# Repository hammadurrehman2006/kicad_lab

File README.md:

# kicad_lab
A collection of KiCad PCB designs developed during my Electronic Engineering degree (2024-28). Includes university projects, personal experiments, and custom components—featuring schematics, layouts, Gerber files, and documentation. Open-source hardware for education, collaboration, and real-world manufacturing.

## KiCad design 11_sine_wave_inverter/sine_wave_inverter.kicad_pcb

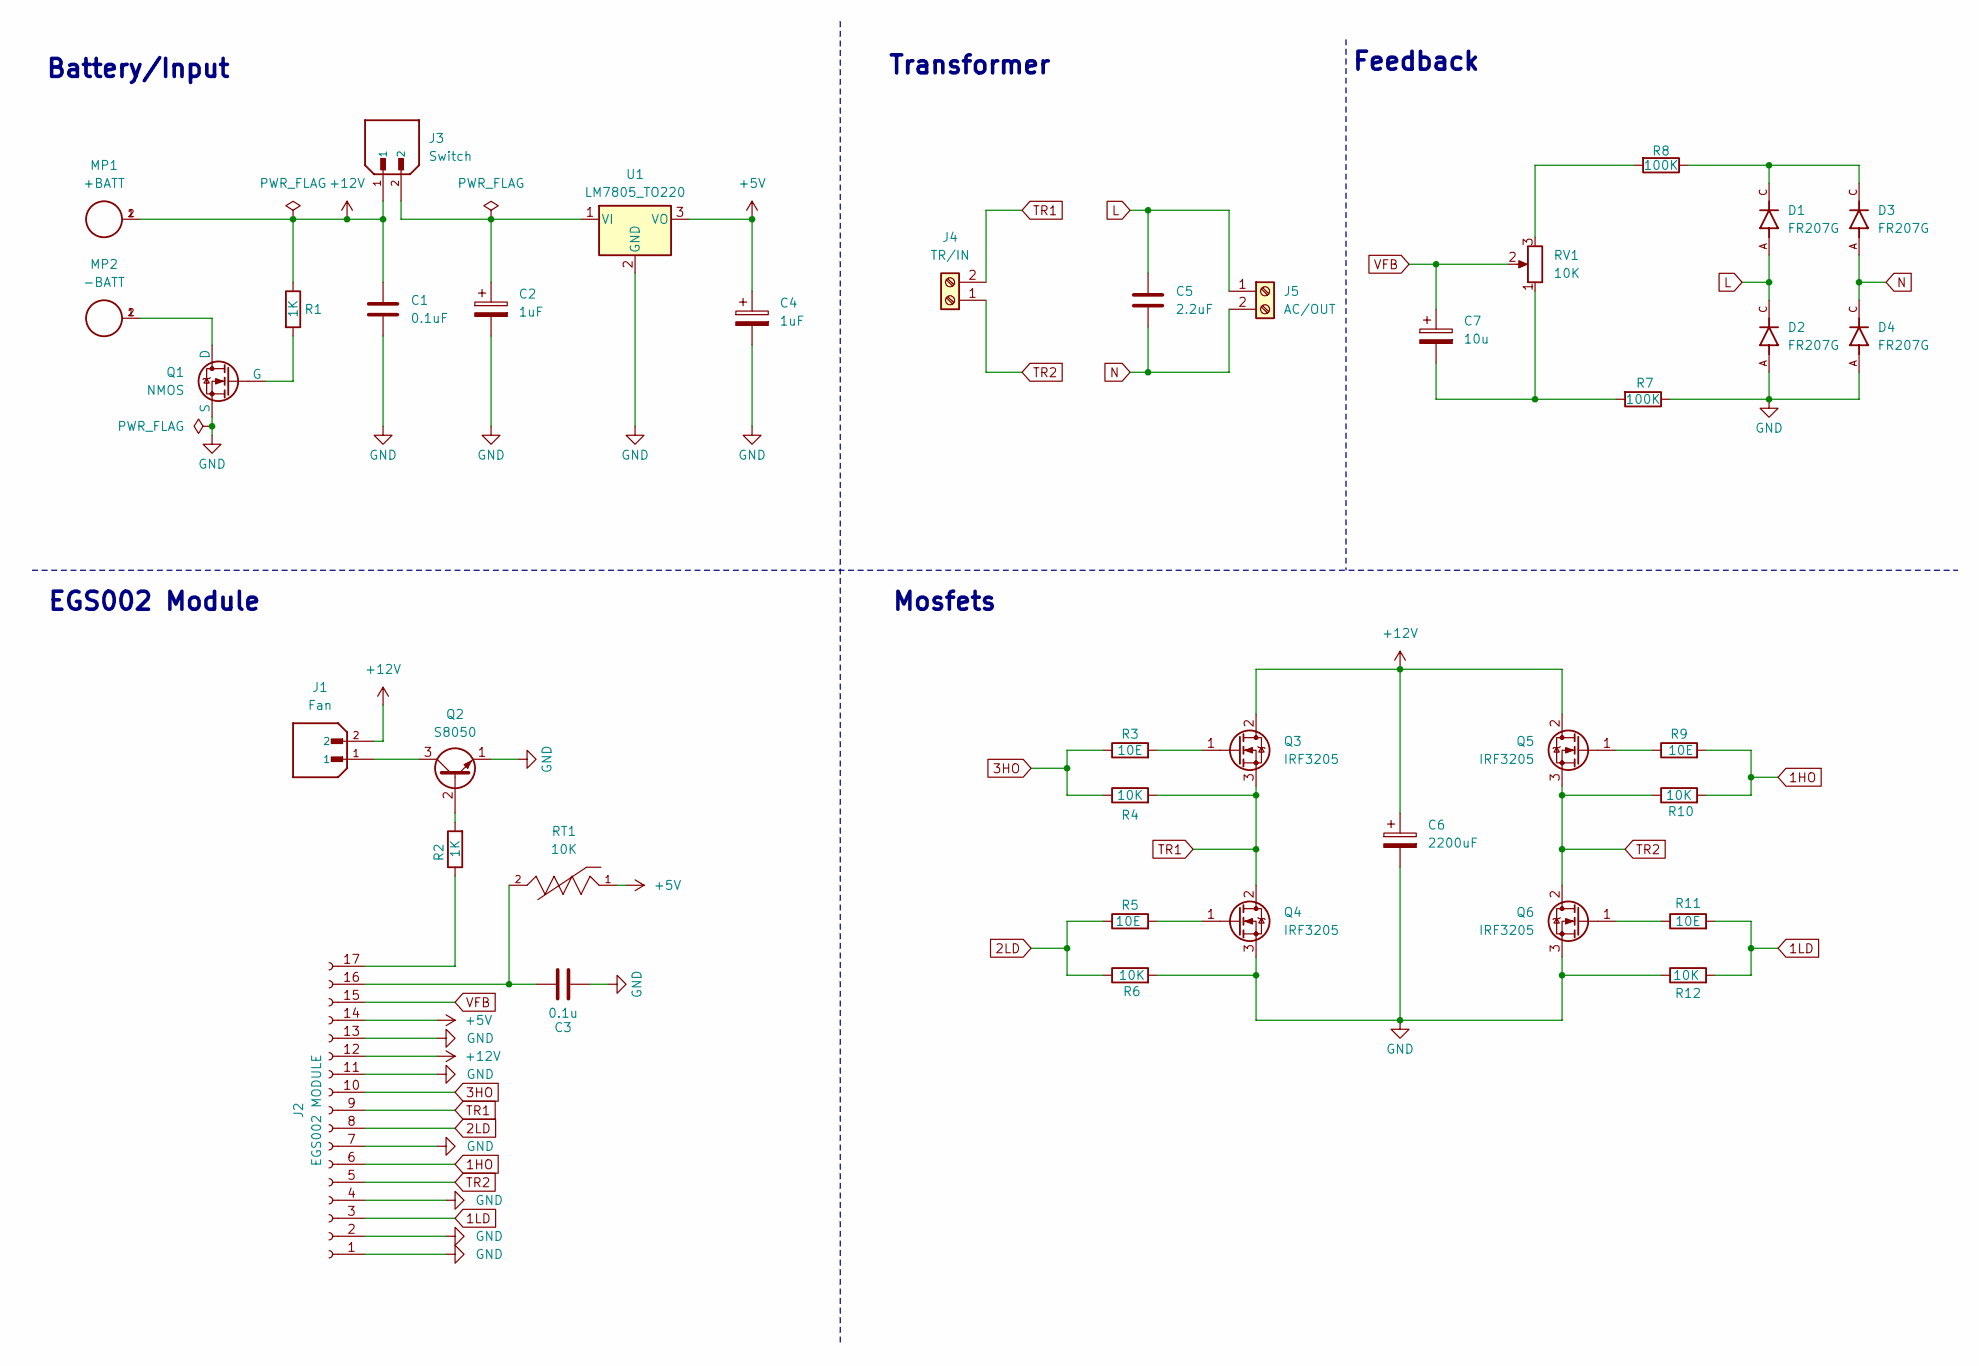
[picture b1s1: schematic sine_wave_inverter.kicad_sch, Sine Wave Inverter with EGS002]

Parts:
C1: 0.1uF; C_Disc_D4.3mm_W1.9mm_P5.00mm
C2, C4: 1uF; CP_Radial_D5.0mm_P2.50mm
C3: 0.1u; C_Disc_D4.3mm_W1.9mm_P5.00mm
C5: 2.2uF; C_Rect_L16.5mm_W6.0mm_P15.00mm_MKT
C6: 2200uF; CP_Radial_D12.5mm_P5.00mm
C7: 10u; CP_Radial_D5.0mm_P2.50mm
D1, D2, D3, D4: FR207G; DIOAD1300W80L670D310; PARTREV F2105
J1: Fan; JST_B2B-XH-A__LF__SN_; PARTREV N/A
J2: EGS002 MODULE; PinSocket_1x17_P2.54mm_Vertical
J3: Switch; JST_B2B-XH-A__LF__SN_; PARTREV N/A
J4: TR/IN; TerminalBlock_bornier-2_P5.08mm
J5: AC/OUT; TerminalBlock_bornier-2_P5.08mm
MP1: +BATT; WA-MTAB_7471287; PART-NUMBER 7471287
MP2: -BATT; WA-MTAB_7471287; PART-NUMBER 7471287
Q1: NMOS; TO-252-2
Q2: S8050; TO-92_Inline
Q3, Q4, Q5, Q6: IRF3205; TO-220-3_Vertical
R1, R2: 1K; R_Axial_DIN0207_L6.3mm_D2.5mm_P7.62mm_Horizontal
R3, R5, R9, R11: 10E; R_Axial_DIN0207_L6.3mm_D2.5mm_P7.62mm_Horizontal
R4, R6, R10, R12: 10K; R_Axial_DIN0207_L6.3mm_D2.5mm_P7.62mm_Horizontal
R7, R8: 100K; R_Axial_DIN0207_L6.3mm_D2.5mm_P7.62mm_Horizontal
RT1: 10K; THERM_NXRT15WB333JA3A016; PARTREV N/A
RV1: 10K; Potentiometer_Bourns_3296W_Vertical
U1: LM7805_TO220; TO-220-3_Vertical

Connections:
1HO: J2.6, R9.2, R10.2
1LD: J2.3, R11.2, R12.2
2LD: J2.8, R5.1, R6.1
3HO: J2.10, R3.1, R4.1
+5V: C4.1, J2.14, RT1.1, U1.3 (VO)
+12V: C1.1, C6.1, J1.2, J2.12, J3.1, MP1.1, MP1.2, Q3.2 (D), Q5.2 (D), R1.1
GND: C1.2, C2.2, C3.2, C4.2, C6.2, D2.A, D4.A, J2.1, J2.2, J2.4, J2.7, J2.11, J2.13, Q1.3 (S), Q2.1 (E), Q4.3 (S), Q6.3 (S), R6.2, R7.1, R12.1, U1.2 (GND)
L: C5.1, D1.A, D2.C, J5.1
N: C5.2, D3.A, D4.C, J5.2
unnamed: C7.2, R7.2, RV1.1
unnamed: D1.C, D3.C, R8.1
unnamed: C3.1, J2.16, RT1.2
unnamed: J2.17, R2.1
unnamed: MP2.1, MP2.2, Q1.1 (D)
unnamed: Q1.2 (G), R1.2
unnamed: Q2.2 (B), R2.2
unnamed: J1.1, Q2.3 (C)
unnamed: Q3.1 (G), R3.2
unnamed: Q4.1 (G), R5.2
unnamed: Q5.1 (G), R9.1
unnamed: Q6.1 (G), R11.1
unnamed: R8.2, RV1.3
unnamed: C2.1, J3.2, U1.1 (VI)
TR1: J2.9, J4.2, Q3.3 (S), Q4.2 (D), R4.2
TR2: J2.5, J4.1, Q5.3 (S), Q6.2 (D), R10.1
VFB: C7.1, J2.15, RV1.2

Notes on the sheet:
Battery/Input
EGS002 Module
Transformer
Feedback
Mosfets

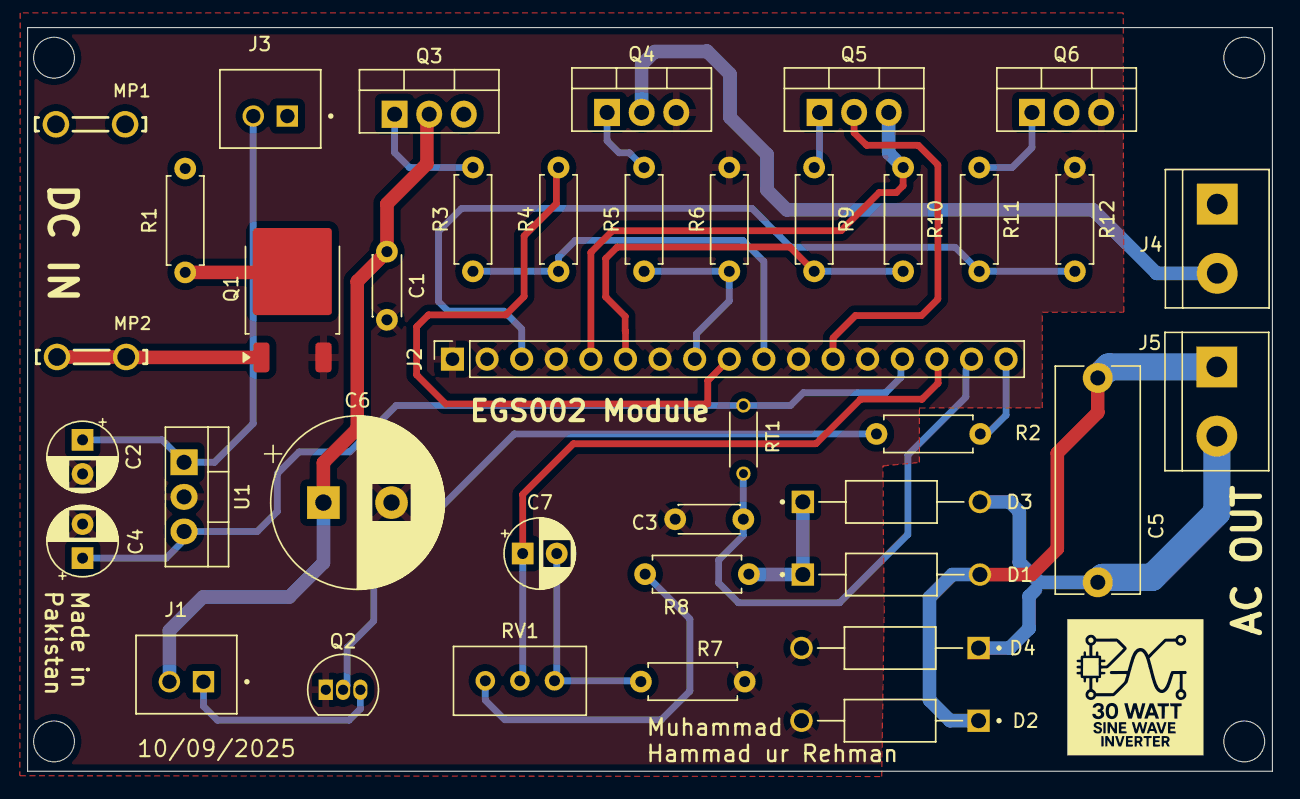
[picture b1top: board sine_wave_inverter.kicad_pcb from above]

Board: 2 copper layers, 91.4 x 54.6 mm, 39 parts (0 on the bottom side), 26 nets.

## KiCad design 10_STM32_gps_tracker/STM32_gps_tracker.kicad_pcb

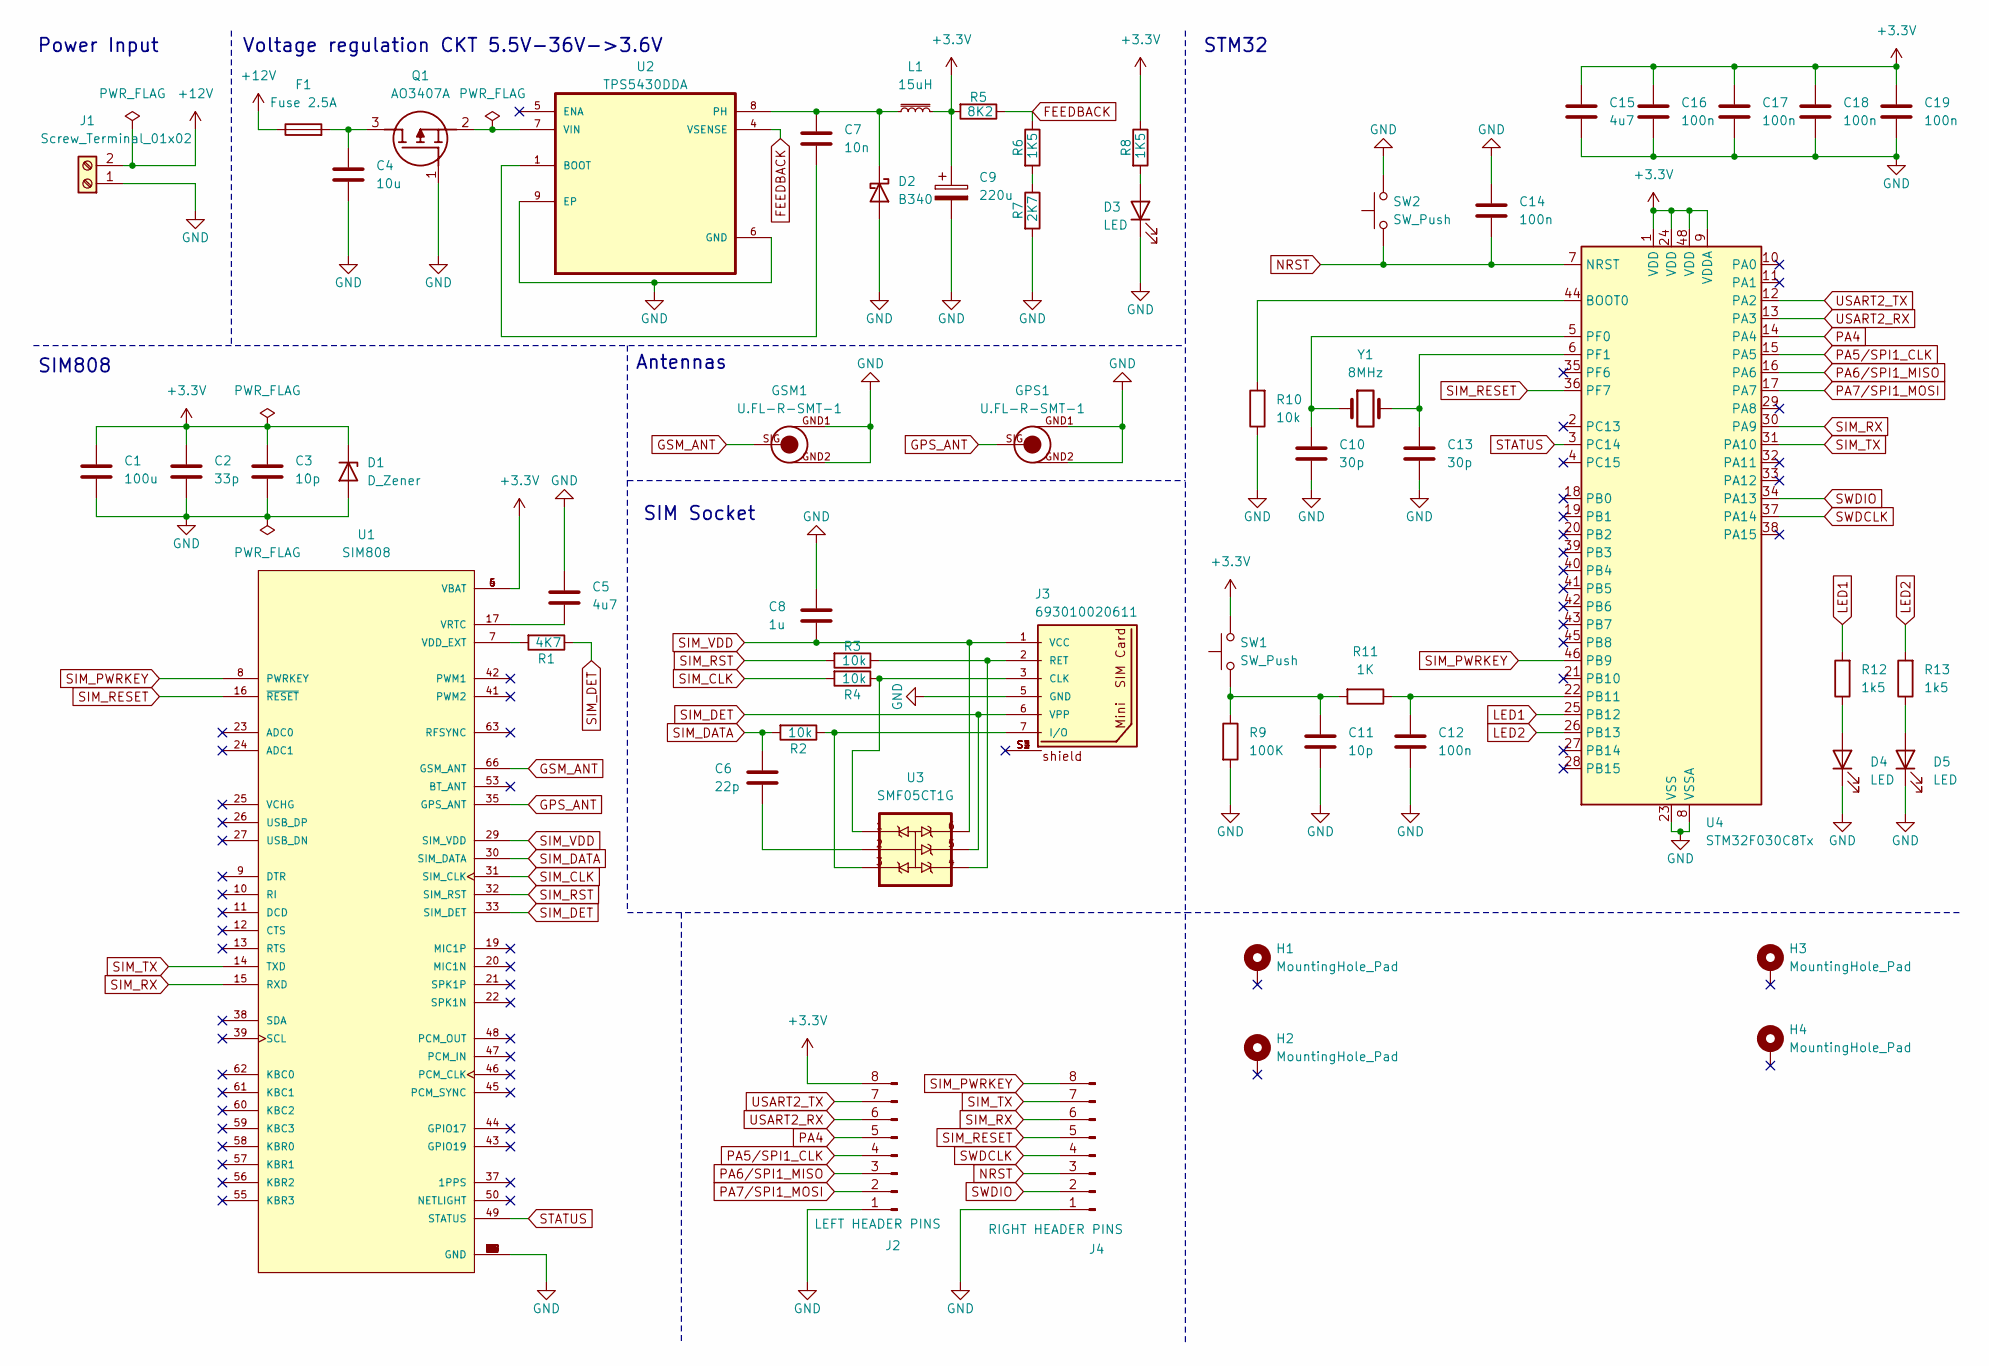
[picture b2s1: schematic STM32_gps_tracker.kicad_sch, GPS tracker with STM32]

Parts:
C1: 100u; C_1206_3216Metric
C2: 33p; C_0402_1005Metric
C3, C11: 10p; C_0402_1005Metric
C4: 10u; C_0805_2012Metric
C5, C15: 4u7; C_0201_0603Metric
C6: 22p; C_0402_1005Metric
C7: 10n; C_0201_0603Metric
C8: 1u; C_0402_1005Metric
C9: 220u; CP_EIA-7343-15_Kemet-W
C10, C13: 30p; C_0402_1005Metric
C12, C14, C16, C17, C18, C19: 100n; C_0402_1005Metric
D1: D_Zener; D_0805_2012Metric
D2: B340; D_SMC
D3, D4, D5: LED; LED_0603_1608Metric
F1: Fuse 2.5A; Fuse_0402_1005Metric
GPS1: U.FL-R-SMT-1
GSM1: U.FL-R-SMT-1
H1, H2, H3, H4: MountingHole_Pad; MountingHole_2.2mm_M2_Pad_Via
J1: Screw_Terminal_01x02; TerminalBlock_bornier-2_P5.08mm
J2: LEFT HEADER PINS; PinHeader_1x08_P2.54mm_Vertical
J3: 693010020611; PART-NUMBER 693010020611
J4: RIGHT HEADER PINS; PinHeader_1x08_P2.54mm_Vertical
L1: 15uH; L_10.4x10.4_H4.8
Q1: AO3407A; SOT95P280X125-3N; Manufacturer_Part_Number AO3407A
R1: 4K7; R_0402_1005Metric
R2, R3, R4, R10: 10k; R_0402_1005Metric
R5: 8K2; R_0805_2012Metric
R6, R8: 1K5; R_0805_2012Metric
R7: 2K7; R_0805_2012Metric
R9: 100K; R_0201_0603Metric
R11: 1K; R_0603_1608Metric
R12, R13: 1k5; R_0805_2012Metric
SW1, SW2: SW_Push; SW_Push_1P1T_NO_CK_KSC6xxJ
U1: SIM808; XCVR_SIM808; PARTREV 1.03
U2: TPS5430DDA; VREG_LM5017MR_NOPB
U3: SMF05CT1G; SOT65P210X110-6N
U4: STM32F030C8Tx; LQFP-48_7x7mm_P0.5mm
Y1: 8MHz; Crystal_SMD_5032-2Pin_5.0x3.2mm

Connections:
+3.3V: C1.1, C2.1, C3.1, C9.1, C15.1, C16.1, C17.1, C18.1, C19.1, D1.1 (K), J2.8, L1.2, R5.2, R8.1, SW1.2, U1.4 (VBAT), U1.5 (VBAT), U1.6 (VBAT), U4.1 (VDD), U4.9 (VDDA), U4.24 (VDD), U4.48 (VDD)
+12V: F1.1, J1.2
FEEDBACK: R5.1, R6.1, U2.4 (VSENSE)
GND: C1.2, C2.2, C3.2, C4.2, C5.1, C8.1, C9.2, C10.2, C11.2, C12.2, C13.2, C14.1, C15.2, C16.2, C17.2, C18.2, C19.2, D1.2 (A), D2.2 (A), D3.1 (K), D4.1 (K), D5.1 (K), GPS1.GND1, GPS1.GND2, GSM1.GND1, GSM1.GND2, J1.1, J2.1, J3.5 (GND), J4.1, Q1.1 (G), R7.2, R9.2, R10.1, SW2.2, U1.1 (GND), U1.2 (GND), U1.3 (GND), U1.18 (GND), U1.28 (GND), U1.34 (GND), U1.36 (GND), U1.40 (GND), U1.51 (GND), U1.52 (GND), U1.54 (GND), U1.64 (GND), U1.65 (GND), U1.67 (GND), U1.68 (GND), U2.6 (GND), U2.9 (EP), U4.8 (VSSA), U4.23 (VSS), U4.47 (VSS)
GPS_ANT: GPS1.SIG, U1.35 (GPS_ANT)
GSM_ANT: GSM1.SIG, U1.66 (GSM_ANT)
LED1: R12.2, U4.25 (PB12)
LED2: R13.2, U4.26 (PB13)
NRST: C14.2, J4.3, SW2.1, U4.7 (NRST)
unnamed: C6.2, U3.2
unnamed: C11.1, R9.1, R11.2, SW1.1
unnamed: C7.2, D2.1 (K), L1.1, U2.8 (PH)
unnamed: D3.2 (A), R8.2
unnamed: D4.2 (A), R12.1
unnamed: D5.2 (A), R13.1
unnamed: J3.3 (CLK), R4.1, U3.1
unnamed: J3.7 (I/O), R2.1, U3.3
unnamed: J3.2 (RET), R3.1, U3.4
unnamed: C4.1, F1.2, Q1.3 (D)
unnamed: Q1.2 (S), U2.7 (VIN)
unnamed: R6.2, R7.1
unnamed: R1.2, U1.7 (VDD_EXT)
unnamed: C5.2, U1.17 (VRTC)
unnamed: C7.1, U2.1 (BOOT)
unnamed: R10.2, U4.44 (BOOT0)
unnamed: C12.1, R11.1, U4.22 (PB11)
unnamed: C10.1, U4.5 (PF0), Y1.1
unnamed: C13.1, U4.6 (PF1), Y1.2
PA4: J2.5, U4.14 (PA4)
PA5/SPI1_CLK: J2.4, U4.15 (PA5)
PA6/SPI1_MISO: J2.3, U4.16 (PA6)
PA7/SPI1_MOSI: J2.2, U4.17 (PA7)
SIM_CLK: R4.2, U1.31 (SIM_CLK)
SIM_DATA: C6.1, R2.2, U1.30 (SIM_DATA)
SIM_DET: J3.6 (VPP), R1.1, U1.33 (SIM_DET), U3.5
SIM_PWRKEY: J4.8, U1.8 (PWRKEY), U4.46 (PB9)
SIM_RESET: J4.5, U1.16 (~RESET), U4.36 (PF7)
SIM_RST: R3.2, U1.32 (SIM_RST)
SIM_RX: J4.6, U1.15 (RXD), U4.30 (PA9)
SIM_TX: J4.7, U1.14 (TXD), U4.31 (PA10)
SIM_VDD: C8.2, J3.1 (VCC), U1.29 (SIM_VDD), U3.6
STATUS: U1.49 (STATUS), U4.3 (PC14)
SWDCLK: J4.4, U4.37 (PA14)
SWDIO: J4.2, U4.34 (PA13)
USART2_RX: J2.6, U4.13 (PA3)
USART2_TX: J2.7, U4.12 (PA2)

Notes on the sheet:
SIM Socket
Power Input
Voltage regulation CKT 5.5V-36V->3.6V
STM32
Antennas
SIM808

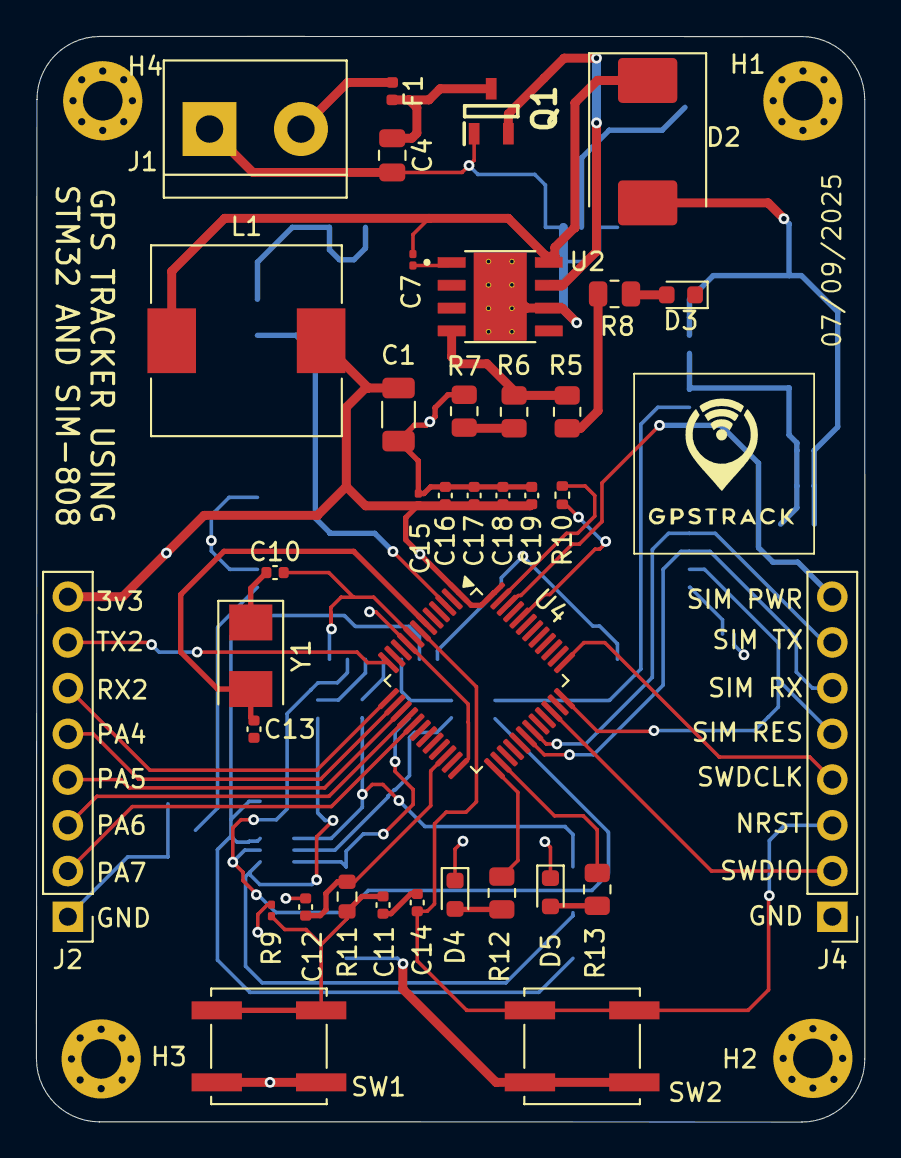
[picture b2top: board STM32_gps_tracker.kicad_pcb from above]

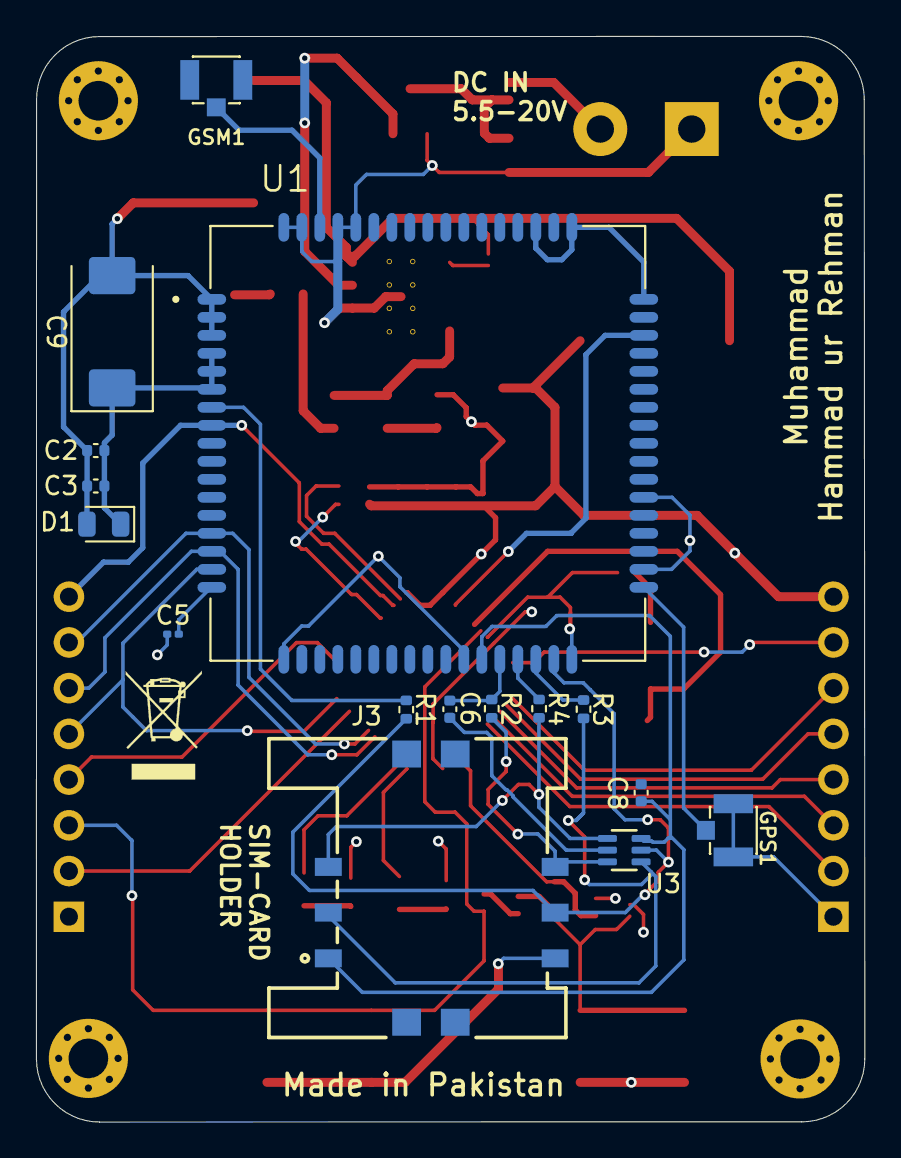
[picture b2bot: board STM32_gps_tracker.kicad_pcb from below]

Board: 4 copper layers, 46.0 x 60.3 mm, 57 parts (16 on the bottom side), 46 nets.

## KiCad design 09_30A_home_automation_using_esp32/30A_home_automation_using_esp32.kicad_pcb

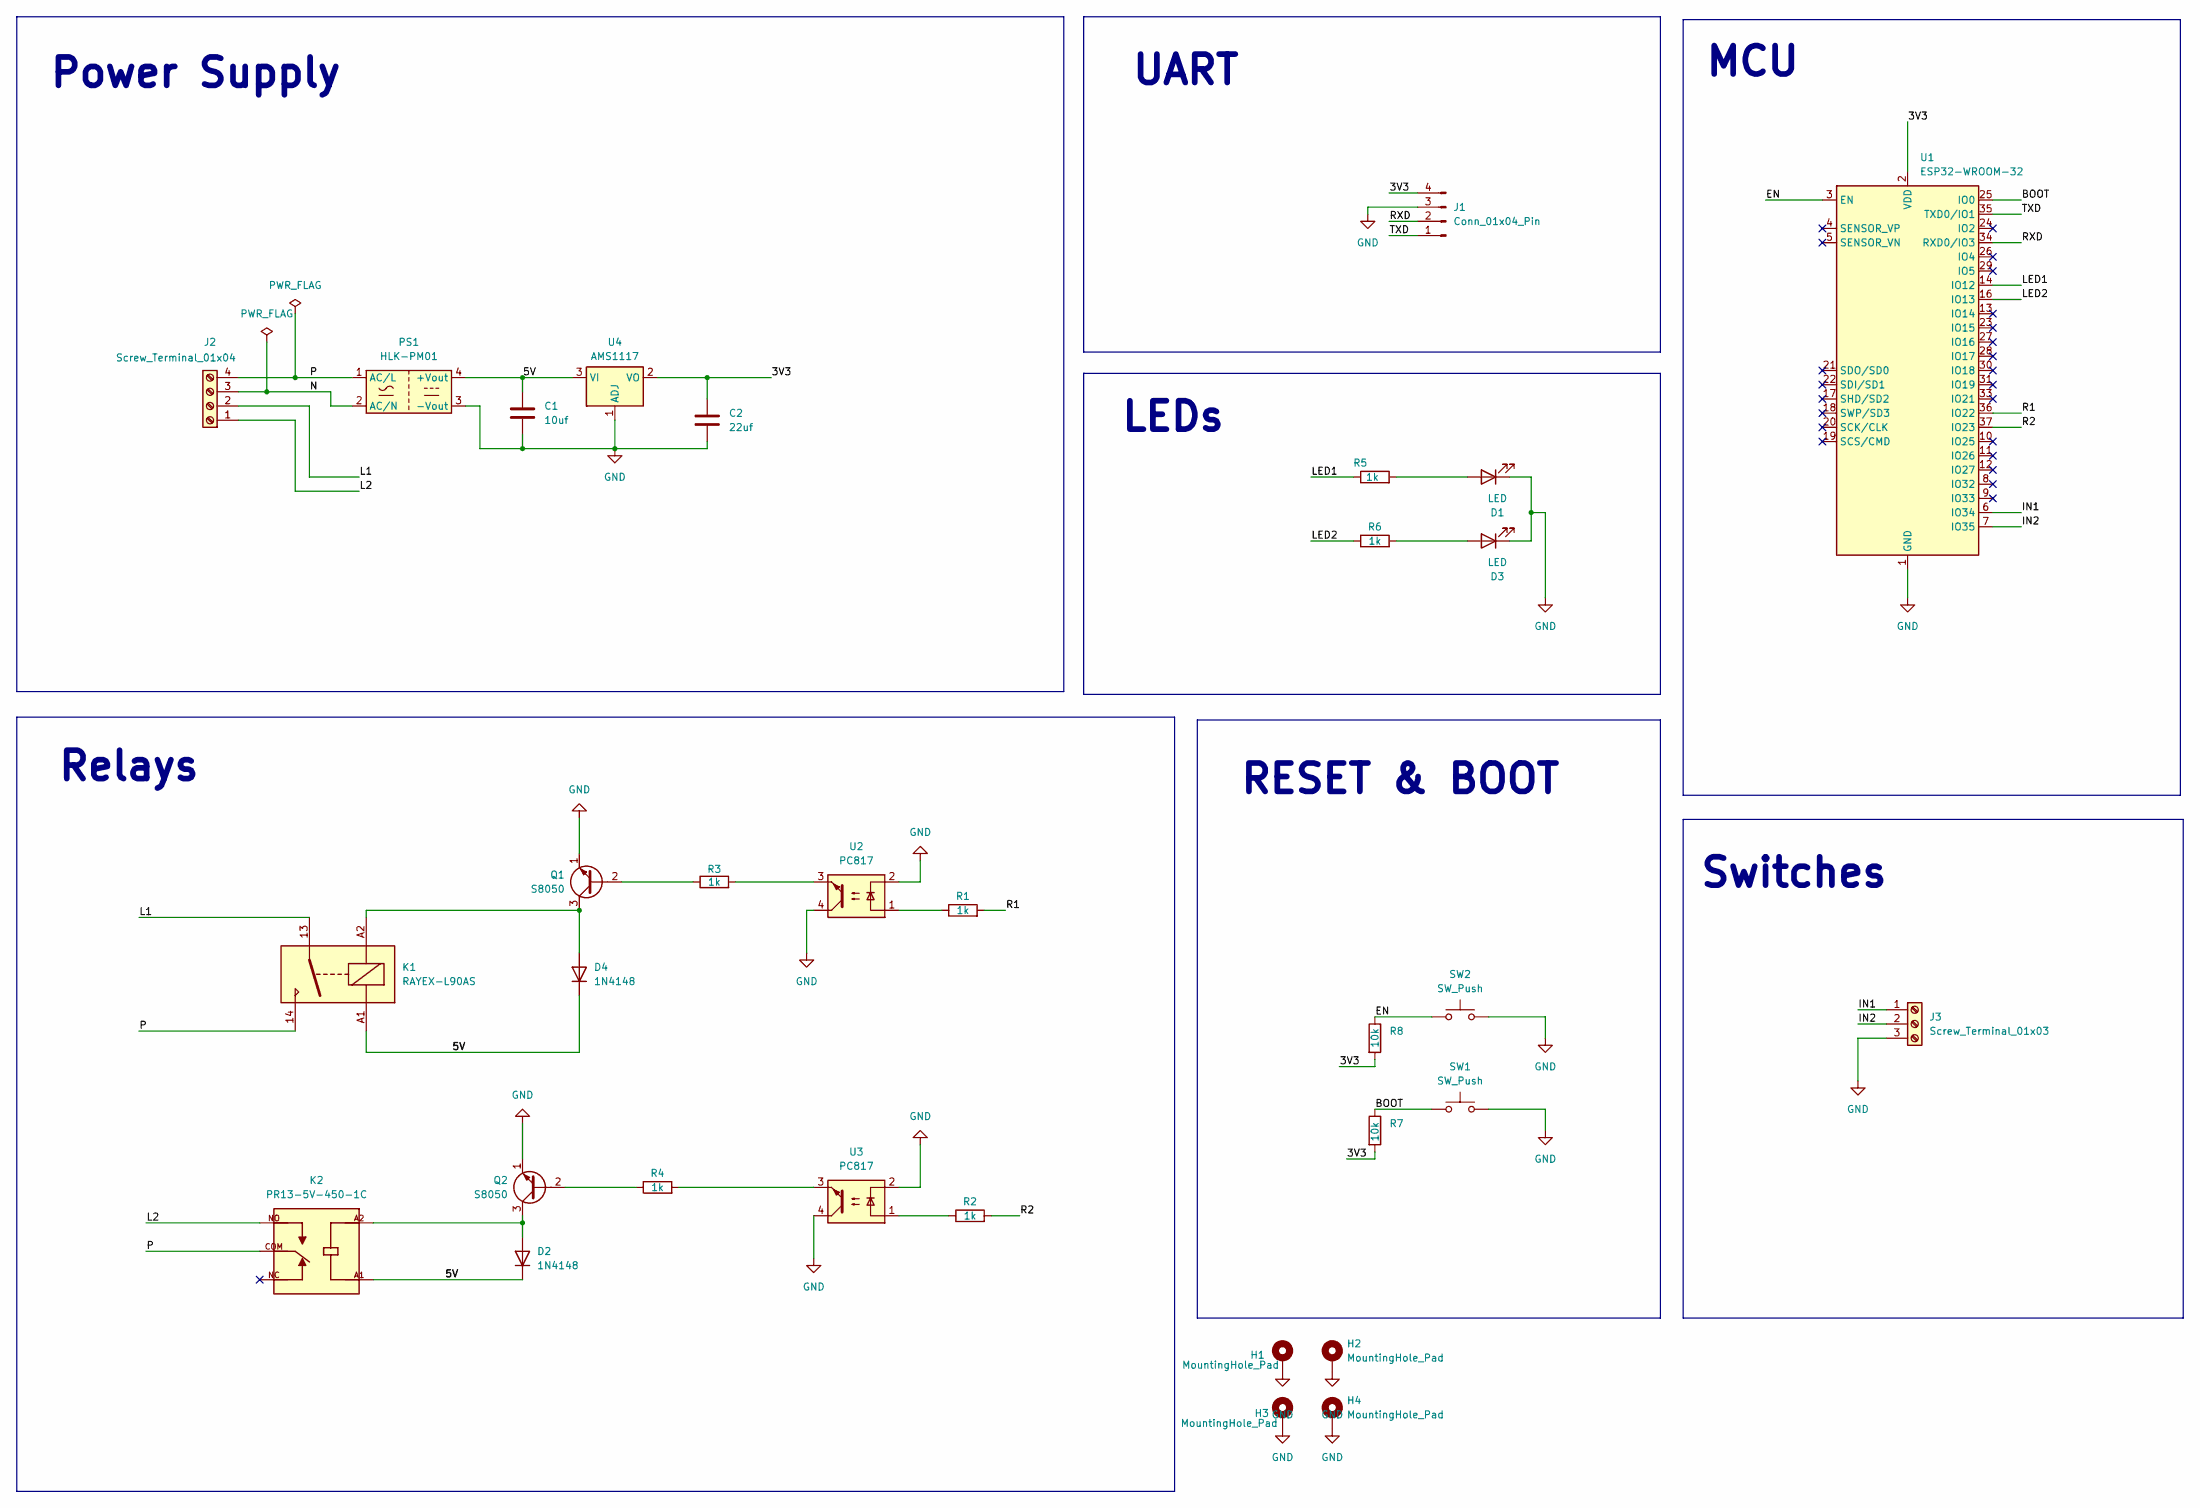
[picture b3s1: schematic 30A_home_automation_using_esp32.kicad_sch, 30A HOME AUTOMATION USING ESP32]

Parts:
C1: 10uf; C_0805_2012Metric
C2: 22uf; C_0805_2012Metric
D1, D3: LED; LED_0805_2012Metric
D2, D4: 1N4148; D_DO-35_SOD27_P7.62mm_Horizontal
H1, H2, H3, H4: MountingHole_Pad; MountingHole_2.7mm_M2.5_Pad_Via
J1: Conn_01x04_Pin; PinHeader_1x04_P2.54mm_Vertical
J2: Screw_Terminal_01x04; TerminalBlock_bornier-4_P5.08mm
J3: Screw_Terminal_01x03; TerminalBlock_bornier-3_P5.08mm
K1: RAYEX-L90AS; Relay_SPST_RAYEX-L90AS
K2: PR13-5V-450-1C; RELAY_PR13-5V-450-1C; PARTREV 1.0
PS1: HLK-PM01; Converter_ACDC_Hi-Link_HLK-PMxx
Q1, Q2: S8050; TO-92_Inline
R1, R2, R3, R4, R5, R6: 1k; R_0805_2012Metric
R7, R8: 10k; R_0805_2012Metric
SW1, SW2: SW_Push; SW_PUSH_6mm
U1: ESP32-WROOM-32
U2, U3: PC817; DIP-4_W7.62mm
U4: AMS1117; SOT-223-3_TabPin2

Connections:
/3V3: C2.1, J1.4, R7.2, R8.2, U1.2 (VDD), U4.2 (VO)
/5V: C1.1, D2.1 (K), D4.1 (K), K1.A1, K2.A1, PS1.4 (+Vout), U4.3 (VI)
/BOOT: R7.1, SW1.1, U1.25 (IO0)
/EN: R8.1, SW2.1, U1.3 (EN)
/IN1: J3.1, U1.6 (IO34)
/IN2: J3.2, U1.7 (IO35)
/L1: J2.2, K1.13
/L2: J2.1, K2.NO
/LED1: R5.1, U1.14 (IO12)
/LED2: R6.1, U1.16 (IO13)
/N: J2.3, PS1.2 (AC/N)
/P: J2.4, K1.14, K2.COM, PS1.1 (AC/L)
/R1: R1.2, U1.36 (IO22)
/R2: R2.2, U1.37 (IO23)
/RXD: J1.2, U1.34 (RXD0/IO3)
/TXD: J1.1, U1.35 (TXD0/IO1)
GND: C1.2, C2.2, D1.1 (K), D3.1 (K), H1.1, H2.1, H3.1, H4.1, J1.3, J3.3, PS1.3 (-Vout), Q1.1 (E), Q2.1 (E), SW1.2, SW2.2, U1.1 (GND), U1.15 (GND), U1.38 (GND), U1.39 (GND), U2.2, U2.4, U3.2, U3.4, U4.1 (ADJ)
unnamed: D1.2 (A), R5.2
unnamed: D2.2 (A), K2.A2, Q2.3 (C)
unnamed: D3.2 (A), R6.2
unnamed: D4.2 (A), K1.A2, Q1.3 (C)
unnamed: Q1.2 (B), R3.1
unnamed: Q2.2 (B), R4.1
unnamed: R1.1, U2.1
unnamed: R2.1, U3.1
unnamed: R3.2, U2.3
unnamed: R4.2, U3.3

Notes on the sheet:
Power Supply
Switches
UART
MCU
LEDs
Relays
RESET & BOOT

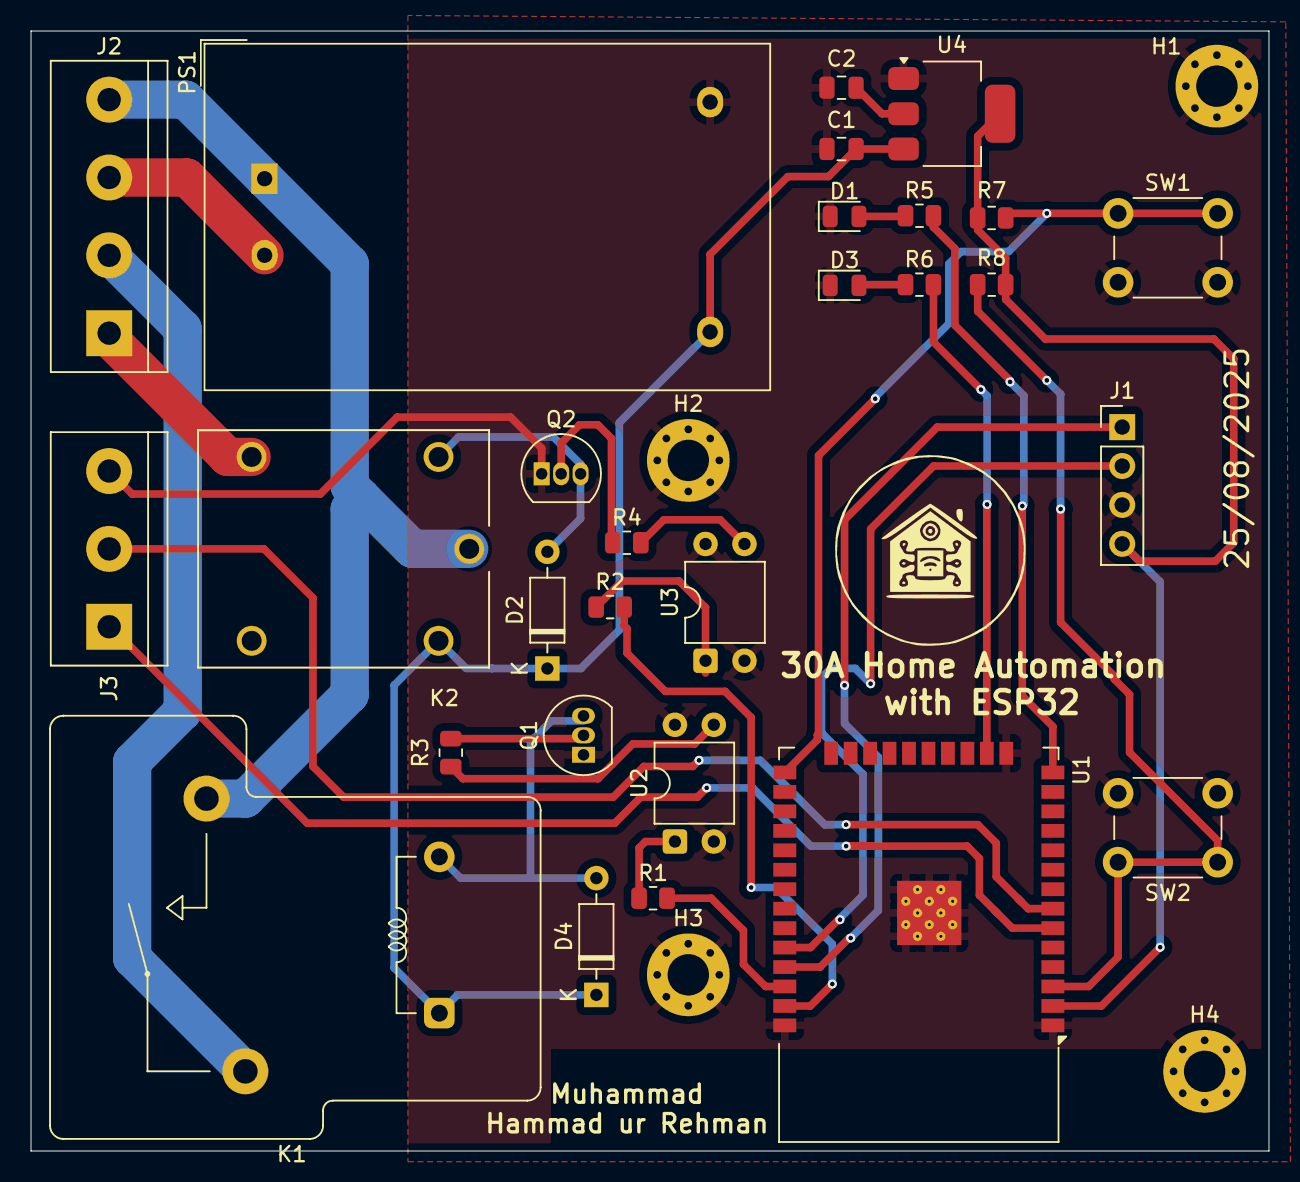
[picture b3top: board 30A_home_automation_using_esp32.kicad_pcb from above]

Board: 2 copper layers, 80.8 x 73.1 mm, 32 parts (0 on the bottom side), 27 nets.

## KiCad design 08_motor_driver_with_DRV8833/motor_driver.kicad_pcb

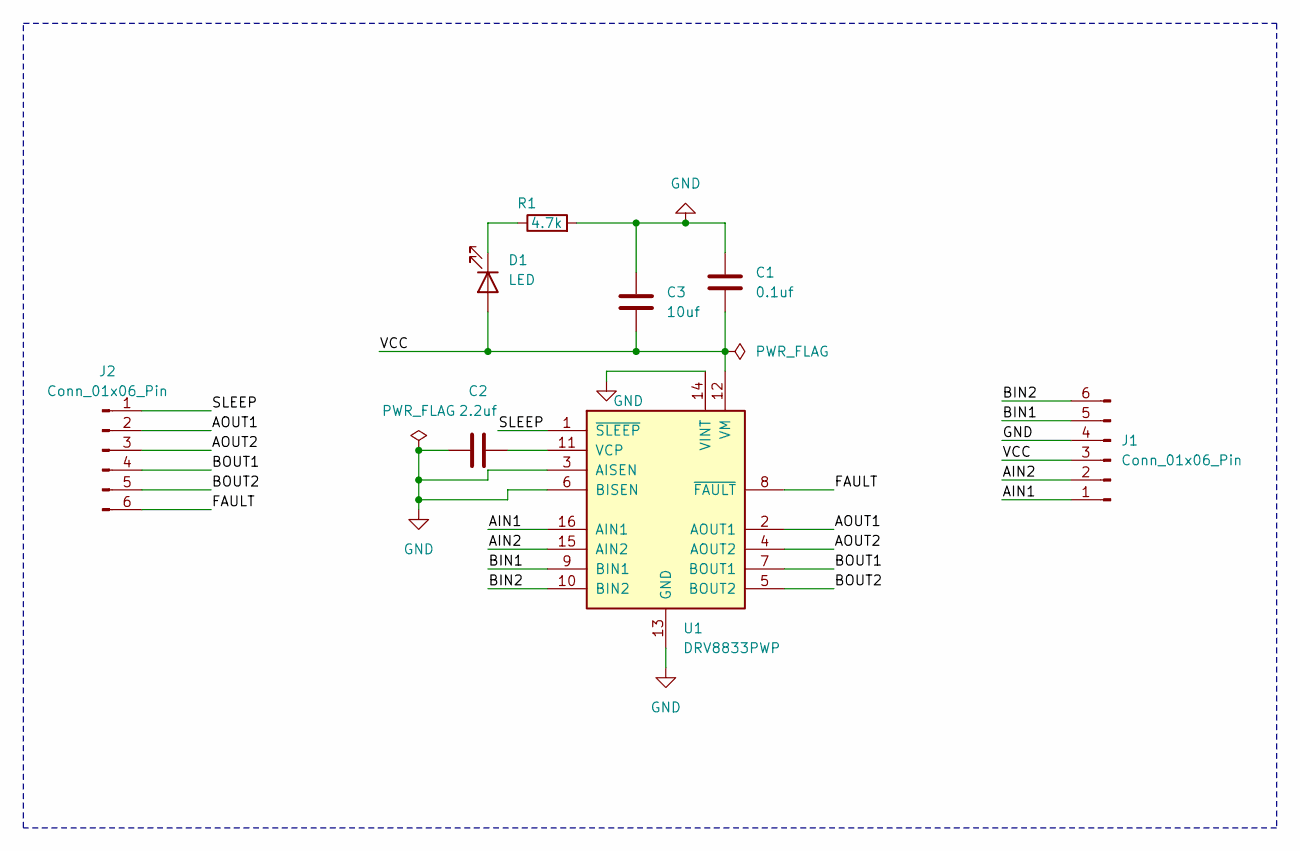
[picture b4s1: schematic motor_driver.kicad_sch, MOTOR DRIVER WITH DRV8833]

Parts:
C1: 0.1uf; C_0805_2012Metric
C2: 2.2uf; C_0805_2012Metric
C3: 10uf; CP_EIA-6032-20_AVX-F
D1: LED; LED_0805_2012Metric
J1, J2: Conn_01x06_Pin; PinHeader_1x06_P2.54mm_Vertical
R1: 4.7k; R_0805_2012Metric
U1: DRV8833PWP; HTSSOP-16-1EP_4.4x5mm_P0.65mm_EP3.4x5mm_Mask2.46x2.31mm_The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

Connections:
/AIN1: J1.1, U1.16 (AIN1)
/AIN2: J1.2, U1.15 (AIN2)
/AOUT1: J2.2, U1.2 (AOUT1)
/AOUT2: J2.3, U1.4 (AOUT2)
/BIN1: J1.5, U1.9 (BIN1)
/BIN2: J1.6, U1.10 (BIN2)
/BOUT1: J2.4, U1.7 (BOUT1)
/BOUT2: J2.5, U1.5 (BOUT2)
/FAULT: J2.6, U1.8 (~FAULT)
/SLEEP: J2.1, U1.1 (~SLEEP)
/VCC: C1.2, C3.2, D1.2 (A), J1.3, U1.12 (VM)
GND: C1.1, C2.1, C3.1, J1.4, R1.2, U1.3 (AISEN), U1.6 (BISEN), U1.13 (GND), U1.14 (VINT), U1.17 (GND)
unnamed: D1.1 (K), R1.1
unnamed: C2.2, U1.11 (VCP)

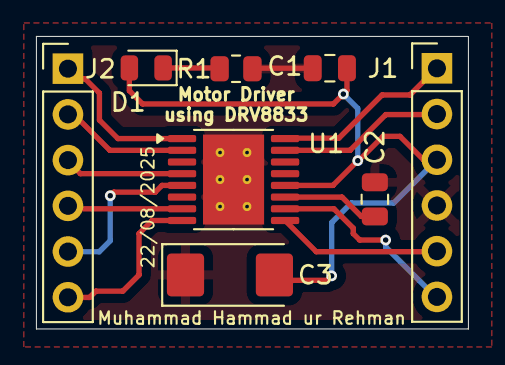
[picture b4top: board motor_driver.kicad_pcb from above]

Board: 2 copper layers, 24.0 x 16.2 mm, 8 parts (0 on the bottom side), 14 nets.

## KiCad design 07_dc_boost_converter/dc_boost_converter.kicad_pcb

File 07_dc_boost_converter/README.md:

# Day 6 – Boost Converter (XL6009)

This is **Day 6** of my **10-Day PCB Design Challenge**.
Today, I designed a **Boost Converter** circuit using the **XL6009 regulator IC** in KiCad.

A boost converter is a **DC-DC step-up regulator** that efficiently converts a lower input voltage into a higher output voltage, making it useful in power supply applications where the input source is lower than the required load voltage.

---

## 📜 Project Overview

This design uses the **XL6009 boost regulator IC** with supporting components to provide a stable adjustable output.

### Key Components:

* **XL6009 Regulator IC** (step-up DC-DC converter)
* **Inductor (33µH)** for energy storage
* **Schottky diode (SS34)** for rectification
* **Capacitors**:

  * Input → 47µF/50V + 1µF
  * Output → 220µF/50V + 1µF
* **Potentiometer (RV1)** to adjust output voltage
* **Resistor (R1)** for feedback reference
* **Connectors** for input & output terminals

---

## 🛠 Tools Used

* **KiCad** → Schematic & PCB Design
* **GitHub** → Version control & documentation

---

## 📂 Files in This Project

* **Schematic & PCB files** (KiCad project)
* **Gerber files** (for fabrication)
* **Drill files**
* **Images** (schematic, PCB layout, 3D preview)

---

## 📸 Project Images

### Schematic

### PCB Layout

### 3D PCB Preview

### 3D PCB Preview without Components

---

## 📬 Repository Info

* **Folder Name:** `07_dc_boost_converter`
* **Author:** Muhammad Hammad ur Rehman
* **License:** Open for learning & educational purposes

---

⚡ With this boost converter, I can efficiently step up DC voltages — making it ideal for powering devices that require higher voltages from lower-voltage sources.

---

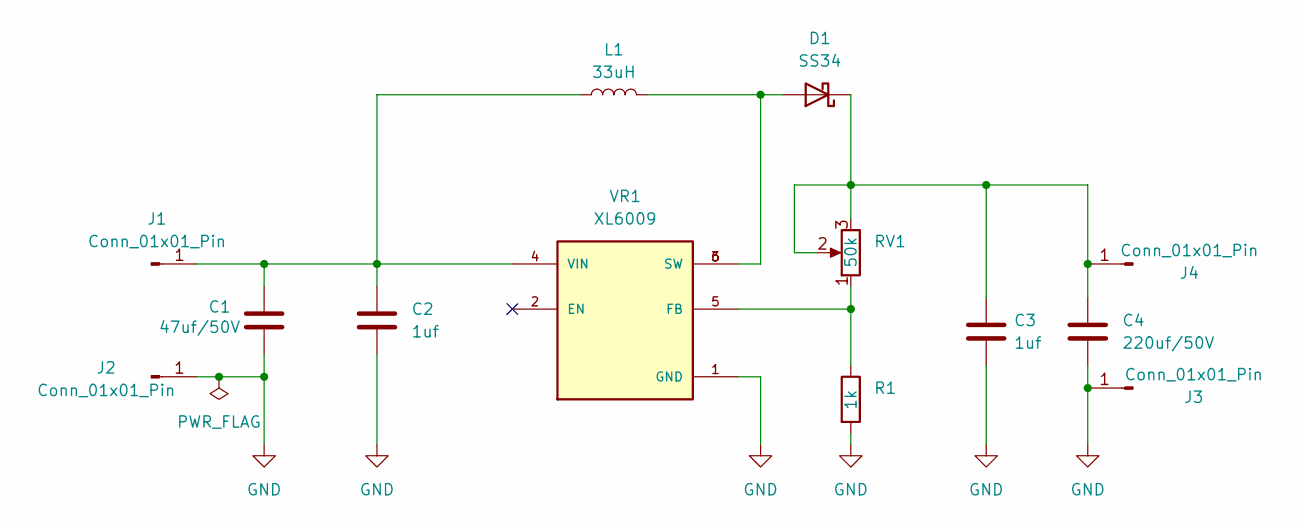
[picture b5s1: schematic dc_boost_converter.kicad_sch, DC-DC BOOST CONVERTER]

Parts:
C1: 47uf/50V; CP_Radial_D6.3mm_P2.50mm
C2, C3: 1uf; C_0805_2012Metric
C4: 220uf/50V; CP_Radial_D6.3mm_P2.50mm
D1: SS34; D_SMA
J1, J2, J3, J4: Conn_01x01_Pin; PinHeader_1x01_P2.54mm_Vertical
L1: 33uH; L_12x12mm_H8mm
R1: 1k; R_1206_3216Metric
RV1: 50k; Potentiometer_Bourns_3296W_Vertical
VR1: XL6009; DPAK170P1435X465-6N; PARTREV 1.1

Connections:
GND: C1.2, C2.2, C3.2, C4.2, J2.1, J3.1, R1.2, VR1.1 (GND)
unnamed: D1.2 (A), L1.2, VR1.3 (SW), VR1.6 (SW)
unnamed: C3.1, C4.1, D1.1 (K), J4.1, RV1.2, RV1.3
unnamed: C1.1, C2.1, J1.1, L1.1, VR1.4 (VIN)
unnamed: R1.1, RV1.1, VR1.5 (FB)

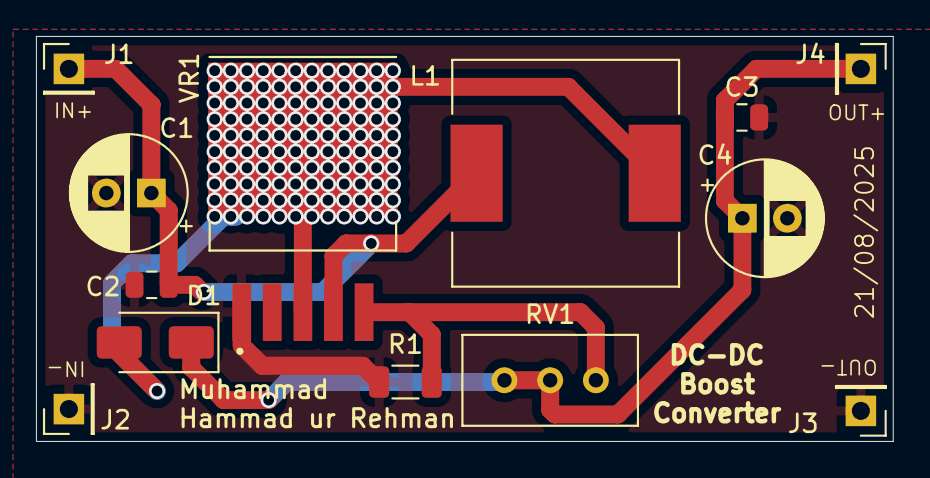
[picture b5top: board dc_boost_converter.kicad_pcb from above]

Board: 2 copper layers, 47.6 x 22.5 mm, 13 parts (0 on the bottom side), 5 nets.
